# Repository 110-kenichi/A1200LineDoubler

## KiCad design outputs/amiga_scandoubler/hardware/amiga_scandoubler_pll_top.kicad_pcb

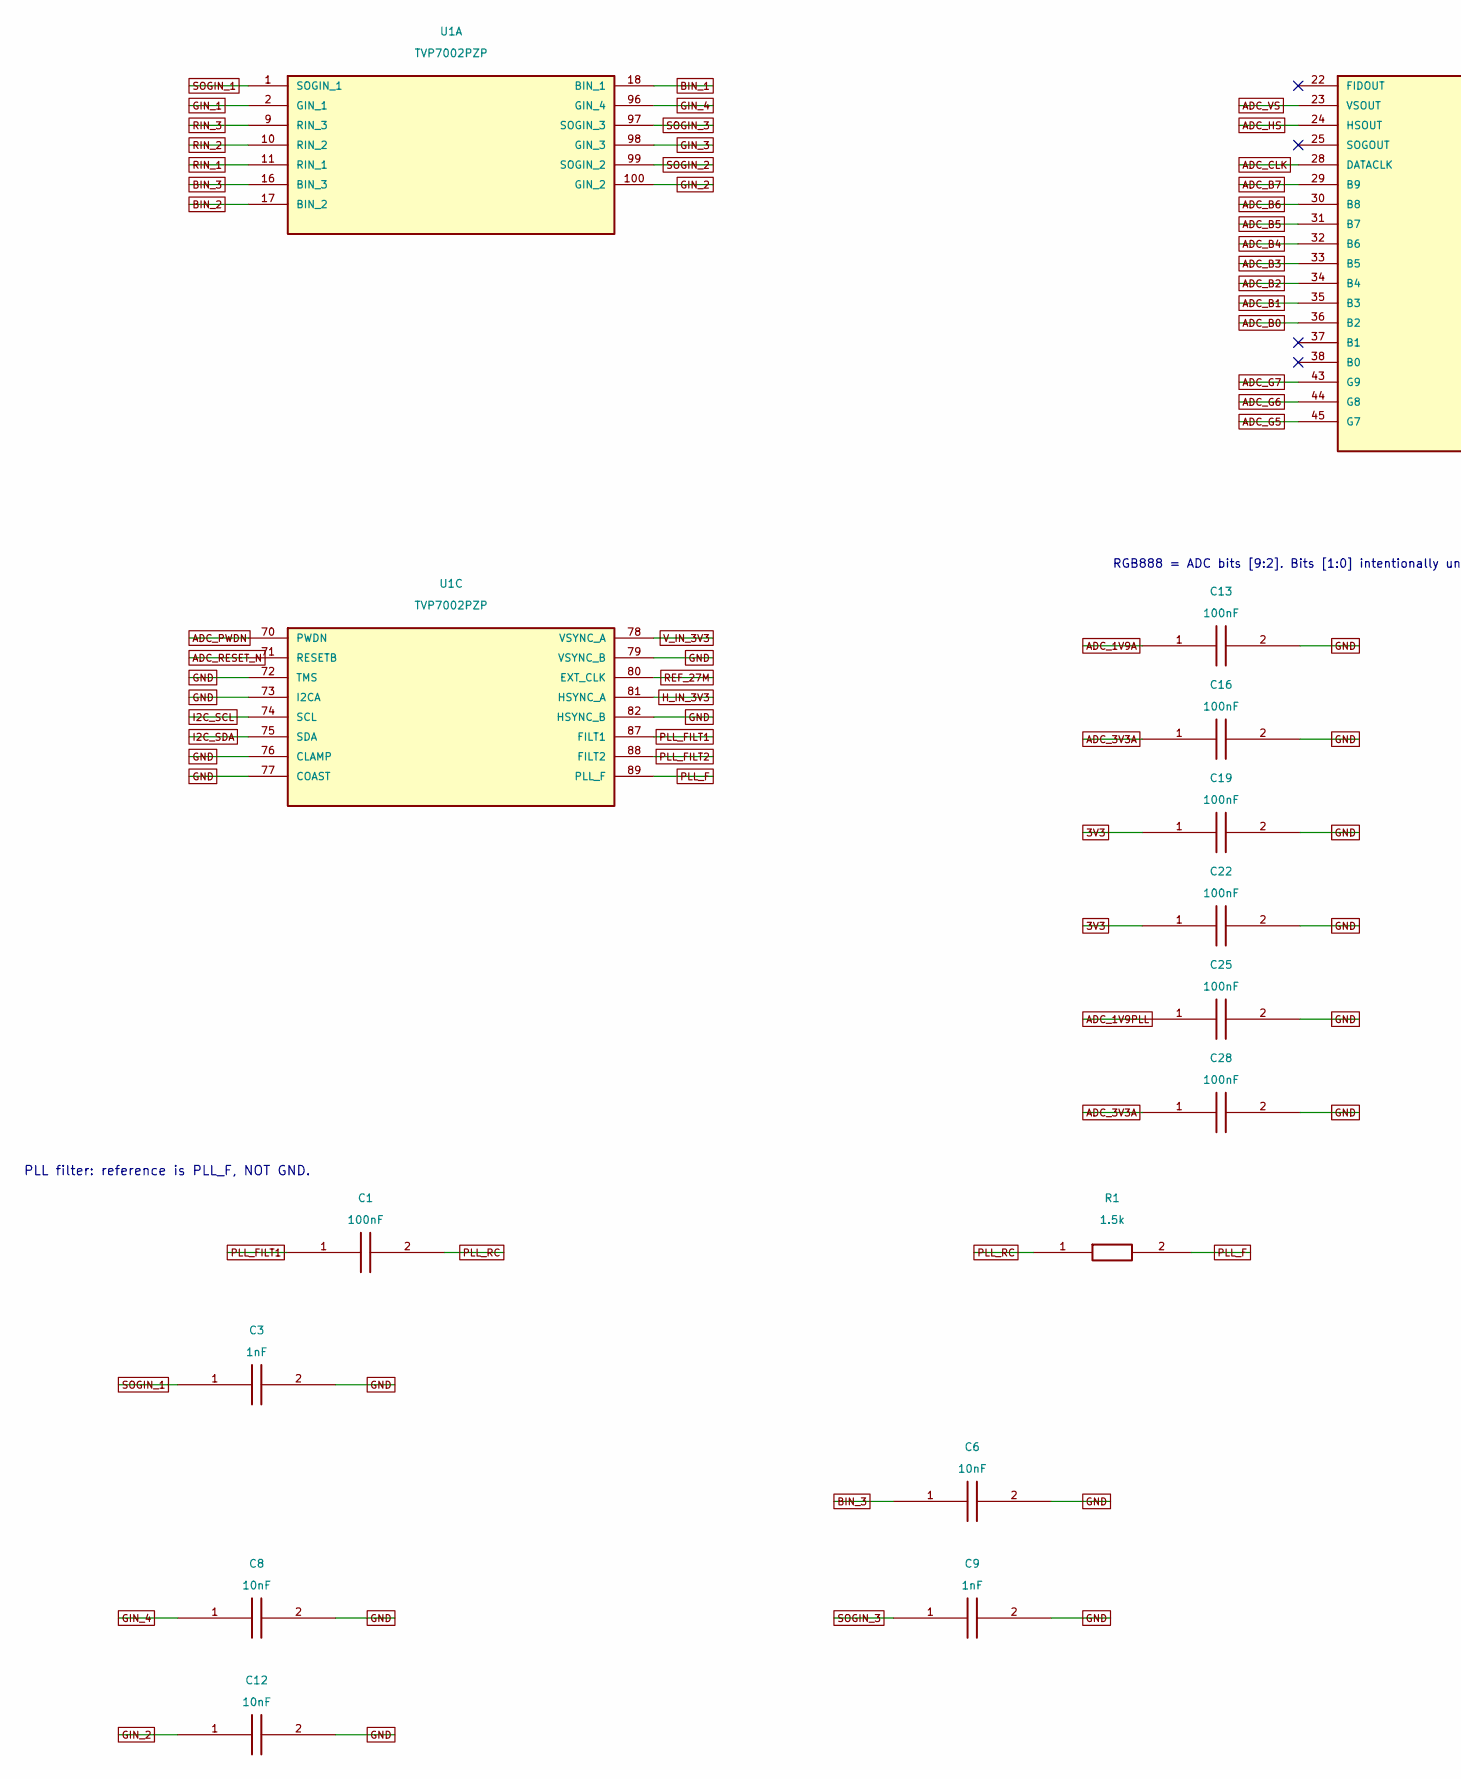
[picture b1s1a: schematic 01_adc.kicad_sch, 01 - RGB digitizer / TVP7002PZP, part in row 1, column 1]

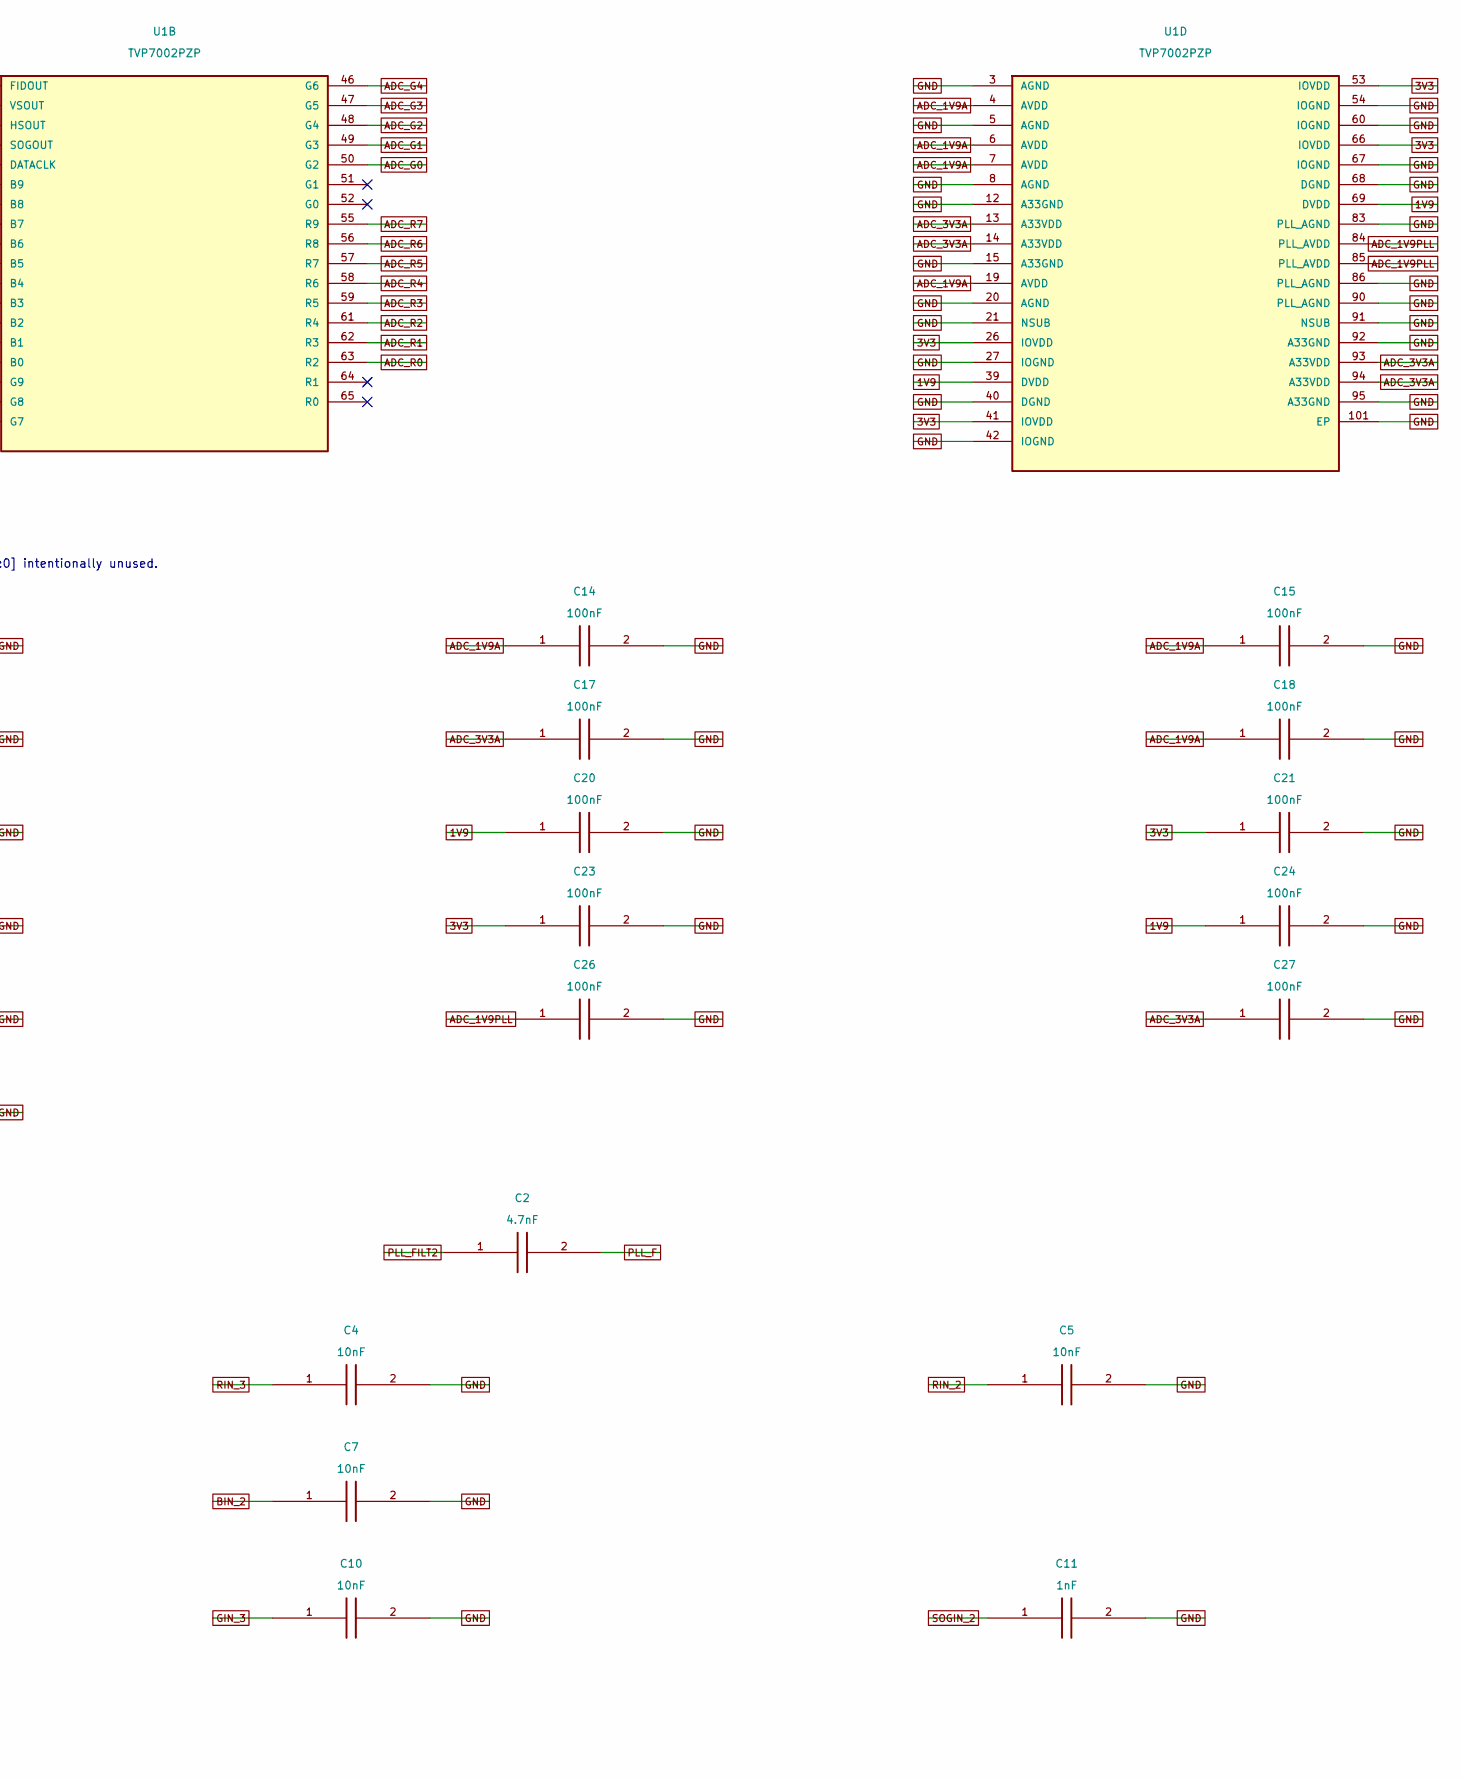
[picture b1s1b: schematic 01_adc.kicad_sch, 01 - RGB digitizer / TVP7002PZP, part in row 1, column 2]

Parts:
C1, C13, C14, C15, C16, C17, C18, C19, C20, C21, C22, C23, C24, C25, C26, C27, C28: 100nF; C_0603_1608Metric; MPN 100nF
C2: 4.7nF; C_0603_1608Metric; MPN 4.7nF
C3, C9, C11: 1nF; C_0603_1608Metric; MPN 1nF
C4, C5, C6, C7, C8, C10, C12: 10nF; C_0603_1608Metric; MPN 10nF
R1: 1.5k; R_0603_1608Metric; MPN 1.5k
U1: TVP7002PZP; TQFP-100_TVP7002_14x14_P0.5_EP6.2; MPN TVP7002PZP; LCSC C3824085

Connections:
1V9: C20.1, C24.1, U1.39 (DVDD), U1.69 (DVDD); also elsewhere on the board
3V3: C19.1, C21.1, C22.1, C23.1, U1.26 (IOVDD), U1.41 (IOVDD), U1.53 (IOVDD), U1.66 (IOVDD); also elsewhere on the board
ADC_1V9A: C13.1, C14.1, C15.1, C18.1, U1.4 (AVDD), U1.6 (AVDD), U1.7 (AVDD), U1.19 (AVDD); also elsewhere on the board
ADC_1V9PLL: C25.1, C26.1, U1.84 (PLL_AVDD), U1.85 (PLL_AVDD); also elsewhere on the board
ADC_3V3A: C16.1, C17.1, C27.1, C28.1, U1.13 (A33VDD), U1.14 (A33VDD), U1.93 (A33VDD), U1.94 (A33VDD); also elsewhere on the board
ADC_B0: U1.36 (B2); also elsewhere on the board
ADC_B1: U1.35 (B3); also elsewhere on the board
ADC_B2: U1.34 (B4); also elsewhere on the board
ADC_B3: U1.33 (B5); also elsewhere on the board
ADC_B4: U1.32 (B6); also elsewhere on the board
ADC_B5: U1.31 (B7); also elsewhere on the board
ADC_B6: U1.30 (B8); also elsewhere on the board
ADC_B7: U1.29 (B9); also elsewhere on the board
ADC_CLK: U1.28 (DATACLK); also elsewhere on the board
ADC_G0: U1.50 (G2); also elsewhere on the board
ADC_G1: U1.49 (G3); also elsewhere on the board
ADC_G2: U1.48 (G4); also elsewhere on the board
ADC_G3: U1.47 (G5); also elsewhere on the board
ADC_G4: U1.46 (G6); also elsewhere on the board
ADC_G5: U1.45 (G7); also elsewhere on the board
ADC_G6: U1.44 (G8); also elsewhere on the board
ADC_G7: U1.43 (G9); also elsewhere on the board
ADC_HS: U1.24 (HSOUT); also elsewhere on the board
ADC_PWDN: U1.70 (PWDN); also elsewhere on the board
ADC_R0: U1.63 (R2); also elsewhere on the board
ADC_R1: U1.62 (R3); also elsewhere on the board
ADC_R2: U1.61 (R4); also elsewhere on the board
ADC_R3: U1.59 (R5); also elsewhere on the board
ADC_R4: U1.58 (R6); also elsewhere on the board
ADC_R5: U1.57 (R7); also elsewhere on the board
ADC_R6: U1.56 (R8); also elsewhere on the board
ADC_R7: U1.55 (R9); also elsewhere on the board
ADC_RESET_N: U1.71 (RESETB); also elsewhere on the board
ADC_VS: U1.23 (VSOUT); also elsewhere on the board
BIN_1: U1.18 (BIN_1); also elsewhere on the board
BIN_2: C7.1, U1.17 (BIN_2)
BIN_3: C6.1, U1.16 (BIN_3)
GIN_1: U1.2 (GIN_1); also elsewhere on the board
GIN_2: C12.1, U1.100 (GIN_2)
GIN_3: C10.1, U1.98 (GIN_3)
GIN_4: C8.1, U1.96 (GIN_4)
GND: C3.2, C4.2, C5.2, C6.2, C7.2, C8.2, C9.2, C10.2, C11.2, C12.2, C13.2, C14.2, C15.2, C16.2, C17.2, C18.2, C19.2, C20.2, C21.2, C22.2, C23.2, C24.2, C25.2, C26.2, C27.2, C28.2, U1.3 (AGND), U1.5 (AGND), U1.8 (AGND), U1.12 (A33GND), U1.15 (A33GND), U1.20 (AGND), U1.21 (NSUB), U1.27 (IOGND), U1.40 (DGND), U1.42 (IOGND), U1.54 (IOGND), U1.60 (IOGND), U1.67 (IOGND), U1.68 (DGND), U1.72 (TMS), U1.73 (I2CA), U1.76 (CLAMP), U1.77 (COAST), U1.79 (VSYNC_B), U1.82 (HSYNC_B), U1.83 (PLL_AGND), U1.86 (PLL_AGND), U1.90 (PLL_AGND), U1.91 (NSUB), U1.92 (A33GND), U1.95 (A33GND), U1.101 (EP); also elsewhere on the board
H_IN_3V3: U1.81 (HSYNC_A); also elsewhere on the board
I2C_SCL: U1.74 (SCL); also elsewhere on the board
I2C_SDA: U1.75 (SDA); also elsewhere on the board
PLL_F: C2.2, R1.2, U1.89 (PLL_F)
PLL_FILT1: C1.1, U1.87 (FILT1)
PLL_FILT2: C2.1, U1.88 (FILT2)
PLL_RC: C1.2, R1.1
REF_27M: U1.80 (EXT_CLK); also elsewhere on the board
RIN_1: U1.11 (RIN_1); also elsewhere on the board
RIN_2: C5.1, U1.10 (RIN_2)
RIN_3: C4.1, U1.9 (RIN_3)
SOGIN_1: C3.1, U1.1 (SOGIN_1)
SOGIN_2: C11.1, U1.99 (SOGIN_2)
SOGIN_3: C9.1, U1.97 (SOGIN_3)
V_IN_3V3: U1.78 (VSYNC_A); also elsewhere on the board

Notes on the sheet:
RGB888 = ADC bits [9:2]. Bits [1:0] intentionally unused.
PLL filter: reference is PLL_F, NOT GND.

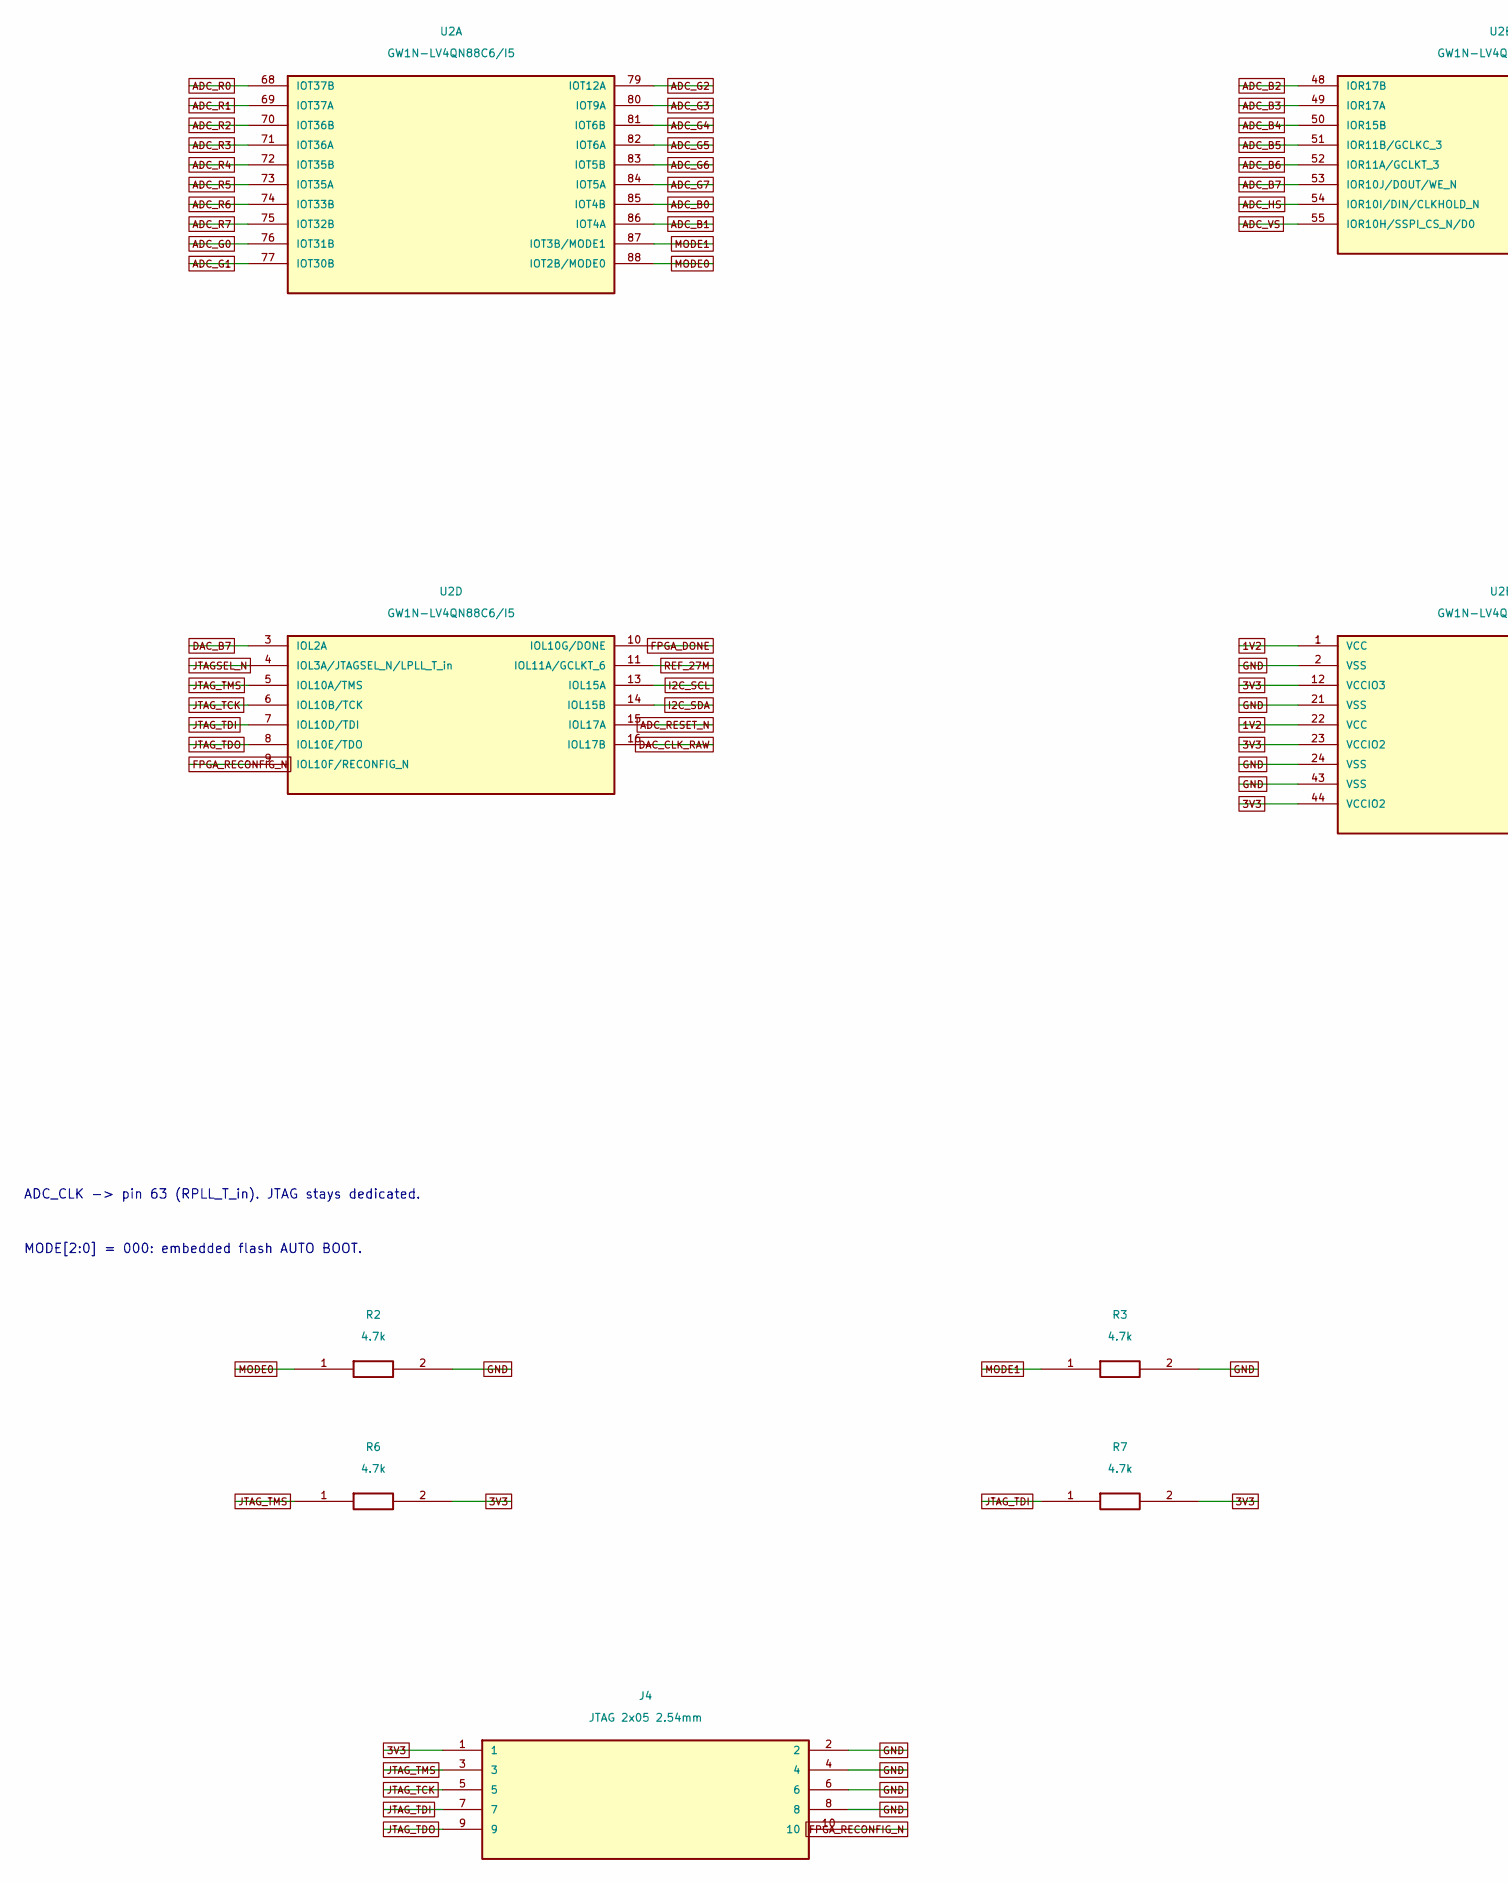
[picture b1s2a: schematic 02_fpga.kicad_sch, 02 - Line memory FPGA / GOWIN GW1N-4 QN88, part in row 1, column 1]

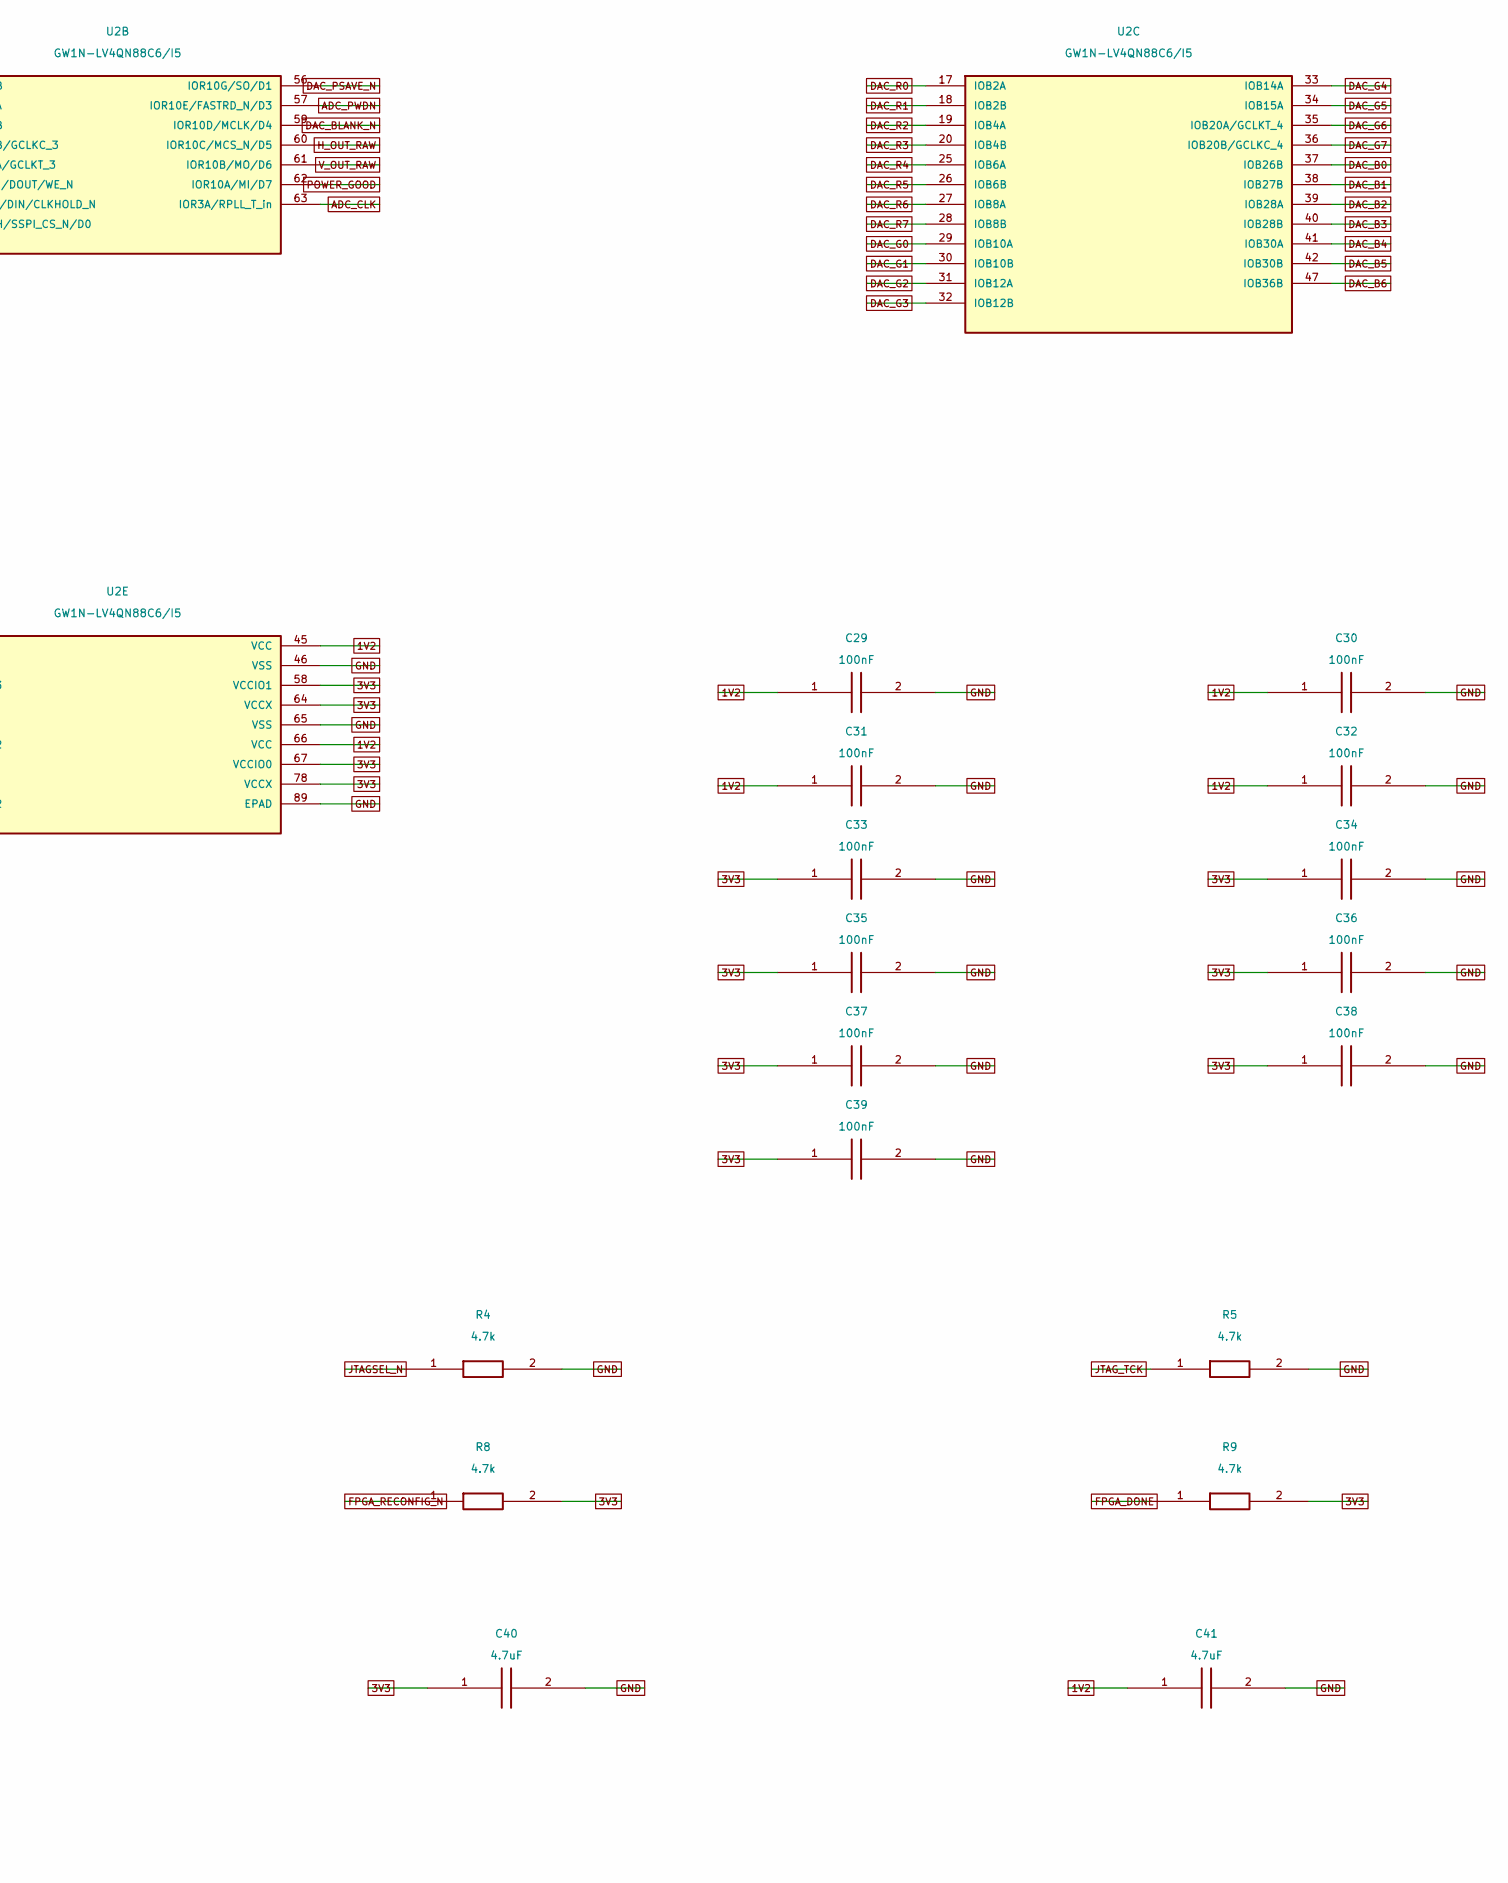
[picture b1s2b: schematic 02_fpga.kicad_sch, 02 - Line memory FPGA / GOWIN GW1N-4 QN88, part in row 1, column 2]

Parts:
C29, C30, C31, C32, C33, C34, C35, C36, C37, C38, C39: 100nF; C_0603_1608Metric; MPN 100nF
C40, C41: 4.7uF; C_0805_2012Metric; MPN 4.7uF
J4: JTAG 2x05 2.54mm; PinHeader_2x05_P2.54mm_Vertical_SMD; MPN JTAG 2x05 2.54mm
R2, R3, R4, R5, R6, R7, R8, R9: 4.7k; R_0603_1608Metric; MPN 4.7k
U2: GW1N-LV4QN88C6/I5; QFN-88_GW1N4_10x10_P0.4_EP6.8; MPN GW1N-LV4QN88C6/I5; LCSC C31900351

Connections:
1V2: C29.1, C30.1, C31.1, C32.1, C41.1, U2.1 (VCC), U2.22 (VCC), U2.45 (VCC), U2.66 (VCC); also elsewhere on the board
3V3: C33.1, C34.1, C35.1, C36.1, C37.1, C38.1, C39.1, C40.1, J4.1, R6.2, R7.2, R8.2, R9.2, U2.12 (VCCIO3), U2.23 (VCCIO2), U2.44 (VCCIO2), U2.58 (VCCIO1), U2.64 (VCCX), U2.67 (VCCIO0), U2.78 (VCCX); also elsewhere on the board
ADC_B0: U2.85 (IOT4B); also elsewhere on the board
ADC_B1: U2.86 (IOT4A); also elsewhere on the board
ADC_B2: U2.48 (IOR17B); also elsewhere on the board
ADC_B3: U2.49 (IOR17A); also elsewhere on the board
ADC_B4: U2.50 (IOR15B); also elsewhere on the board
ADC_B5: U2.51 (IOR11B/GCLKC_3); also elsewhere on the board
ADC_B6: U2.52 (IOR11A/GCLKT_3); also elsewhere on the board
ADC_B7: U2.53 (IOR10J/DOUT/WE_N); also elsewhere on the board
ADC_CLK: U2.63 (IOR3A/RPLL_T_in); also elsewhere on the board
ADC_G0: U2.76 (IOT31B); also elsewhere on the board
ADC_G1: U2.77 (IOT30B); also elsewhere on the board
ADC_G2: U2.79 (IOT12A); also elsewhere on the board
ADC_G3: U2.80 (IOT9A); also elsewhere on the board
ADC_G4: U2.81 (IOT6B); also elsewhere on the board
ADC_G5: U2.82 (IOT6A); also elsewhere on the board
ADC_G6: U2.83 (IOT5B); also elsewhere on the board
ADC_G7: U2.84 (IOT5A); also elsewhere on the board
ADC_HS: U2.54 (IOR10I/DIN/CLKHOLD_N); also elsewhere on the board
ADC_PWDN: U2.57 (IOR10E/FASTRD_N/D3); also elsewhere on the board
ADC_R0: U2.68 (IOT37B); also elsewhere on the board
ADC_R1: U2.69 (IOT37A); also elsewhere on the board
ADC_R2: U2.70 (IOT36B); also elsewhere on the board
ADC_R3: U2.71 (IOT36A); also elsewhere on the board
ADC_R4: U2.72 (IOT35B); also elsewhere on the board
ADC_R5: U2.73 (IOT35A); also elsewhere on the board
ADC_R6: U2.74 (IOT33B); also elsewhere on the board
ADC_R7: U2.75 (IOT32B); also elsewhere on the board
ADC_RESET_N: U2.15 (IOL17A); also elsewhere on the board
ADC_VS: U2.55 (IOR10H/SSPI_CS_N/D0); also elsewhere on the board
DAC_B0: U2.37 (IOB26B); also elsewhere on the board
DAC_B1: U2.38 (IOB27B); also elsewhere on the board
DAC_B2: U2.39 (IOB28A); also elsewhere on the board
DAC_B3: U2.40 (IOB28B); also elsewhere on the board
DAC_B4: U2.41 (IOB30A); also elsewhere on the board
DAC_B5: U2.42 (IOB30B); also elsewhere on the board
DAC_B6: U2.47 (IOB36B); also elsewhere on the board
DAC_B7: U2.3 (IOL2A); also elsewhere on the board
DAC_BLANK_N: U2.59 (IOR10D/MCLK/D4); also elsewhere on the board
DAC_CLK_RAW: U2.16 (IOL17B); also elsewhere on the board
DAC_G0: U2.29 (IOB10A); also elsewhere on the board
DAC_G1: U2.30 (IOB10B); also elsewhere on the board
DAC_G2: U2.31 (IOB12A); also elsewhere on the board
DAC_G3: U2.32 (IOB12B); also elsewhere on the board
DAC_G4: U2.33 (IOB14A); also elsewhere on the board
DAC_G5: U2.34 (IOB15A); also elsewhere on the board
DAC_G6: U2.35 (IOB20A/GCLKT_4); also elsewhere on the board
DAC_G7: U2.36 (IOB20B/GCLKC_4); also elsewhere on the board
DAC_PSAVE_N: U2.56 (IOR10G/SO/D1); also elsewhere on the board
DAC_R0: U2.17 (IOB2A); also elsewhere on the board
DAC_R1: U2.18 (IOB2B); also elsewhere on the board
DAC_R2: U2.19 (IOB4A); also elsewhere on the board
DAC_R3: U2.20 (IOB4B); also elsewhere on the board
DAC_R4: U2.25 (IOB6A); also elsewhere on the board
DAC_R5: U2.26 (IOB6B); also elsewhere on the board
DAC_R6: U2.27 (IOB8A); also elsewhere on the board
DAC_R7: U2.28 (IOB8B); also elsewhere on the board
FPGA_DONE: R9.1, U2.10 (IOL10G/DONE)
FPGA_RECONFIG_N: J4.10, R8.1, U2.9 (IOL10F/RECONFIG_N)
GND: C29.2, C30.2, C31.2, C32.2, C33.2, C34.2, C35.2, C36.2, C37.2, C38.2, C39.2, C40.2, C41.2, J4.2, J4.4, J4.6, J4.8, R2.2, R3.2, R4.2, R5.2, U2.2 (VSS), U2.21 (VSS), U2.24 (VSS), U2.43 (VSS), U2.46 (VSS), U2.65 (VSS), U2.89 (EPAD); also elsewhere on the board
H_OUT_RAW: U2.60 (IOR10C/MCS_N/D5); also elsewhere on the board
I2C_SCL: U2.13 (IOL15A); also elsewhere on the board
I2C_SDA: U2.14 (IOL15B); also elsewhere on the board
JTAGSEL_N: R4.1, U2.4 (IOL3A/JTAGSEL_N/LPLL_T_in)
JTAG_TCK: J4.5, R5.1, U2.6 (IOL10B/TCK)
JTAG_TDI: J4.7, R7.1, U2.7 (IOL10D/TDI)
JTAG_TDO: J4.9, U2.8 (IOL10E/TDO)
JTAG_TMS: J4.3, R6.1, U2.5 (IOL10A/TMS)
MODE0: R2.1, U2.88 (IOT2B/MODE0)
MODE1: R3.1, U2.87 (IOT3B/MODE1)
POWER_GOOD: U2.62 (IOR10A/MI/D7); also elsewhere on the board
REF_27M: U2.11 (IOL11A/GCLKT_6); also elsewhere on the board
V_OUT_RAW: U2.61 (IOR10B/MO/D6); also elsewhere on the board

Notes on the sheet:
ADC_CLK -> pin 63 (RPLL_T_in). JTAG stays dedicated.
MODE[2:0] = 000: embedded flash AUTO BOOT.

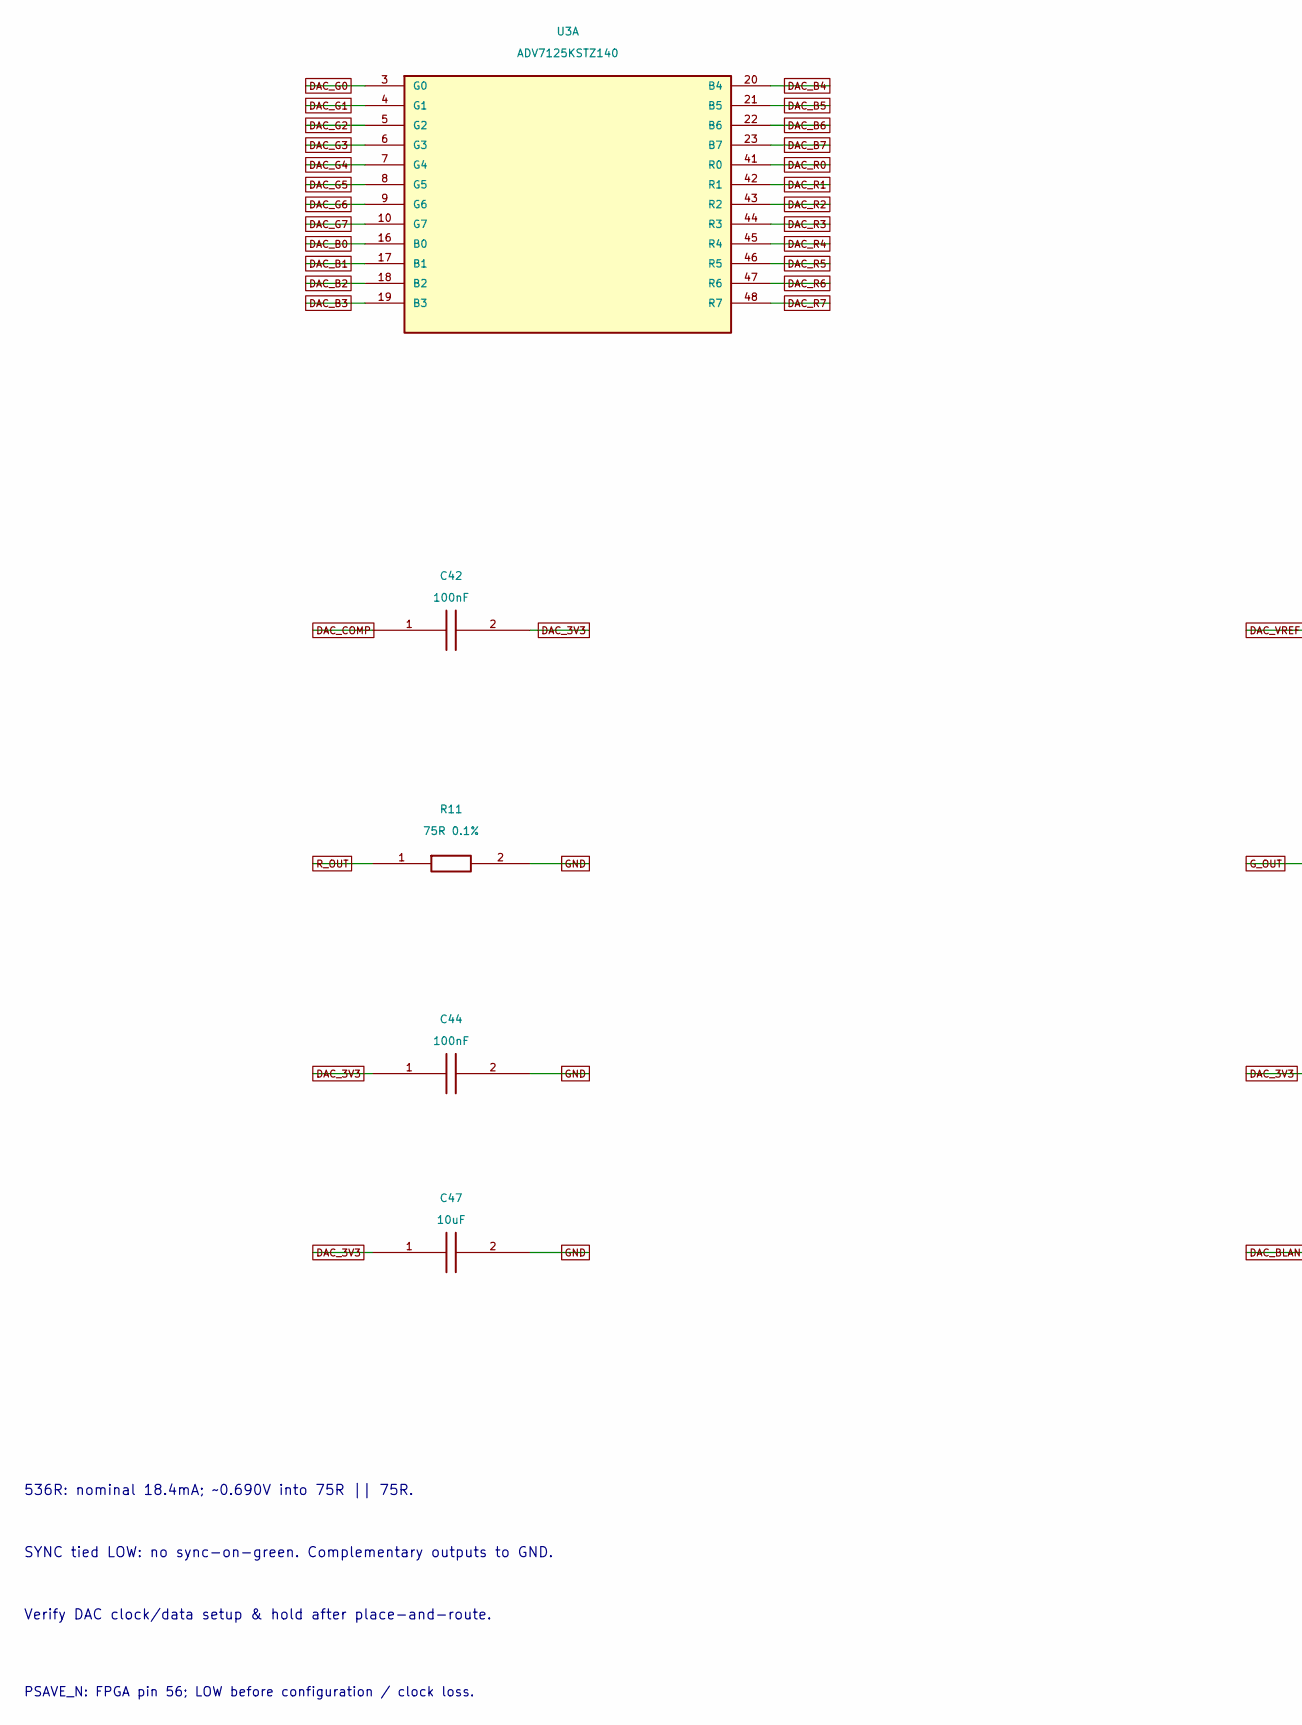
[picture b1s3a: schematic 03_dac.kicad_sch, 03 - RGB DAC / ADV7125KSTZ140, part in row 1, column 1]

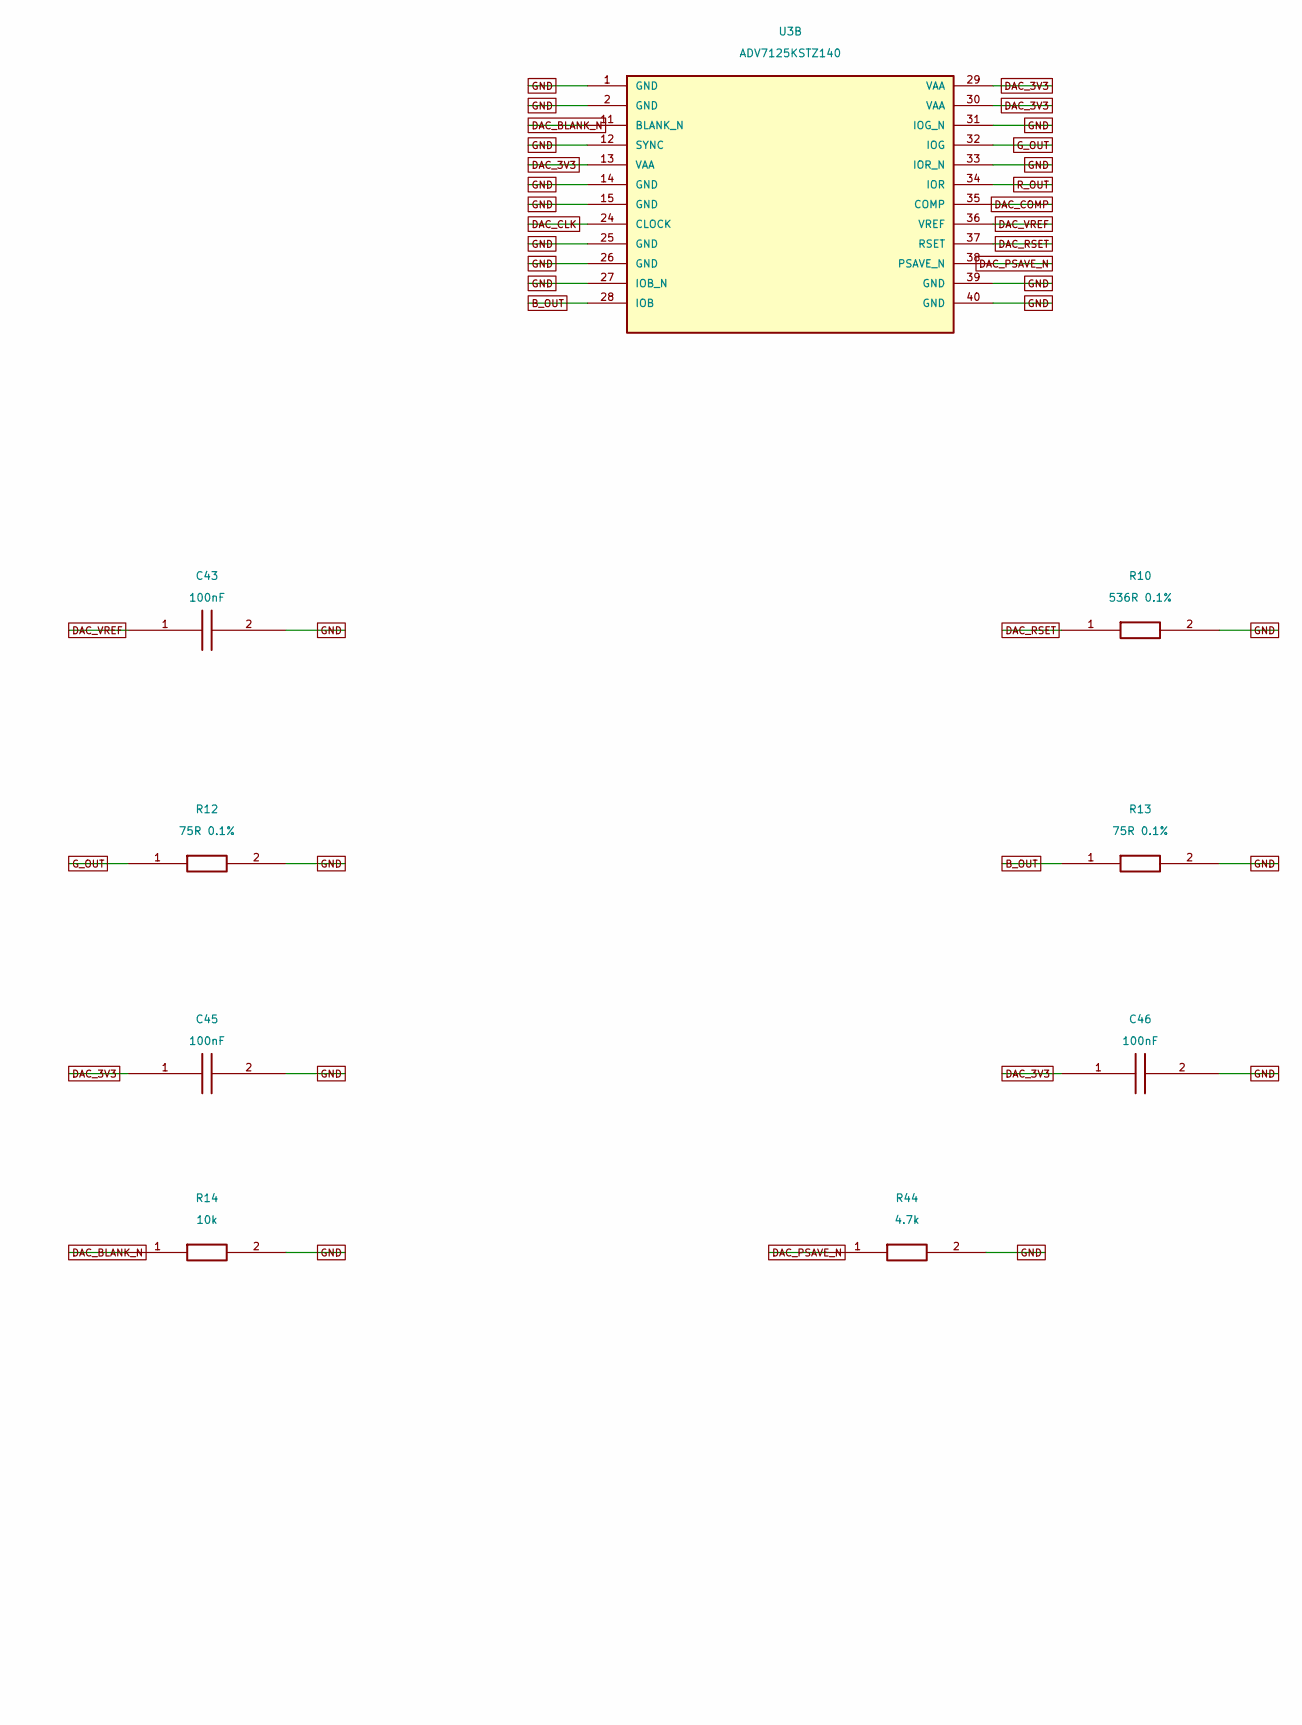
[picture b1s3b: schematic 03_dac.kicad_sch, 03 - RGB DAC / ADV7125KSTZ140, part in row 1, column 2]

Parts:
C42, C43, C44, C45, C46: 100nF; C_0603_1608Metric; MPN 100nF
C47: 10uF; C_0805_2012Metric; MPN 10uF
R10: 536R 0.1%; R_0603_1608Metric; MPN 536R 0.1%
R11, R12, R13: 75R 0.1%; R_0603_1608Metric; MPN 75R 0.1%
R14: 10k; R_0603_1608Metric; MPN 10k
R44: 4.7k; R_0603_1608Metric; MPN 4.7k
U3: ADV7125KSTZ140; LQFP-48_7x7mm_P0.5mm; MPN ADV7125KSTZ140; LCSC C9668

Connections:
B_OUT: R13.1, U3.28 (IOB); also elsewhere on the board
DAC_3V3: C42.2, C44.1, C45.1, C46.1, C47.1, U3.13 (VAA), U3.29 (VAA), U3.30 (VAA); also elsewhere on the board
DAC_B0: U3.16 (B0); also elsewhere on the board
DAC_B1: U3.17 (B1); also elsewhere on the board
DAC_B2: U3.18 (B2); also elsewhere on the board
DAC_B3: U3.19 (B3); also elsewhere on the board
DAC_B4: U3.20 (B4); also elsewhere on the board
DAC_B5: U3.21 (B5); also elsewhere on the board
DAC_B6: U3.22 (B6); also elsewhere on the board
DAC_B7: U3.23 (B7); also elsewhere on the board
DAC_BLANK_N: R14.1, U3.11 (BLANK_N); also elsewhere on the board
DAC_CLK: U3.24 (CLOCK); also elsewhere on the board
DAC_COMP: C42.1, U3.35 (COMP)
DAC_G0: U3.3 (G0); also elsewhere on the board
DAC_G1: U3.4 (G1); also elsewhere on the board
DAC_G2: U3.5 (G2); also elsewhere on the board
DAC_G3: U3.6 (G3); also elsewhere on the board
DAC_G4: U3.7 (G4); also elsewhere on the board
DAC_G5: U3.8 (G5); also elsewhere on the board
DAC_G6: U3.9 (G6); also elsewhere on the board
DAC_G7: U3.10 (G7); also elsewhere on the board
DAC_PSAVE_N: R44.1, U3.38 (PSAVE_N); also elsewhere on the board
DAC_R0: U3.41 (R0); also elsewhere on the board
DAC_R1: U3.42 (R1); also elsewhere on the board
DAC_R2: U3.43 (R2); also elsewhere on the board
DAC_R3: U3.44 (R3); also elsewhere on the board
DAC_R4: U3.45 (R4); also elsewhere on the board
DAC_R5: U3.46 (R5); also elsewhere on the board
DAC_R6: U3.47 (R6); also elsewhere on the board
DAC_R7: U3.48 (R7); also elsewhere on the board
DAC_RSET: R10.1, U3.37 (RSET)
DAC_VREF: C43.1, U3.36 (VREF)
GND: C43.2, C44.2, C45.2, C46.2, C47.2, R10.2, R11.2, R12.2, R13.2, R14.2, R44.2, U3.1 (GND), U3.2 (GND), U3.12 (SYNC), U3.14 (GND), U3.15 (GND), U3.25 (GND), U3.26 (GND), U3.27 (IOB_N), U3.31 (IOG_N), U3.33 (IOR_N), U3.39 (GND), U3.40 (GND); also elsewhere on the board
G_OUT: R12.1, U3.32 (IOG); also elsewhere on the board
R_OUT: R11.1, U3.34 (IOR); also elsewhere on the board

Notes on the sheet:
536R: nominal 18.4mA; ~0.690V into 75R || 75R.
SYNC tied LOW: no sync-on-green. Complementary outputs to GND.
Verify DAC clock/data setup & hold after place-and-route.
PSAVE_N: FPGA pin 56; LOW before configuration / clock loss.
